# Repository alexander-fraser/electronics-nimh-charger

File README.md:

# electronics-nimh-charger
A simple NIMH AA or AAA battery charger based on bigclivedotcom's design.

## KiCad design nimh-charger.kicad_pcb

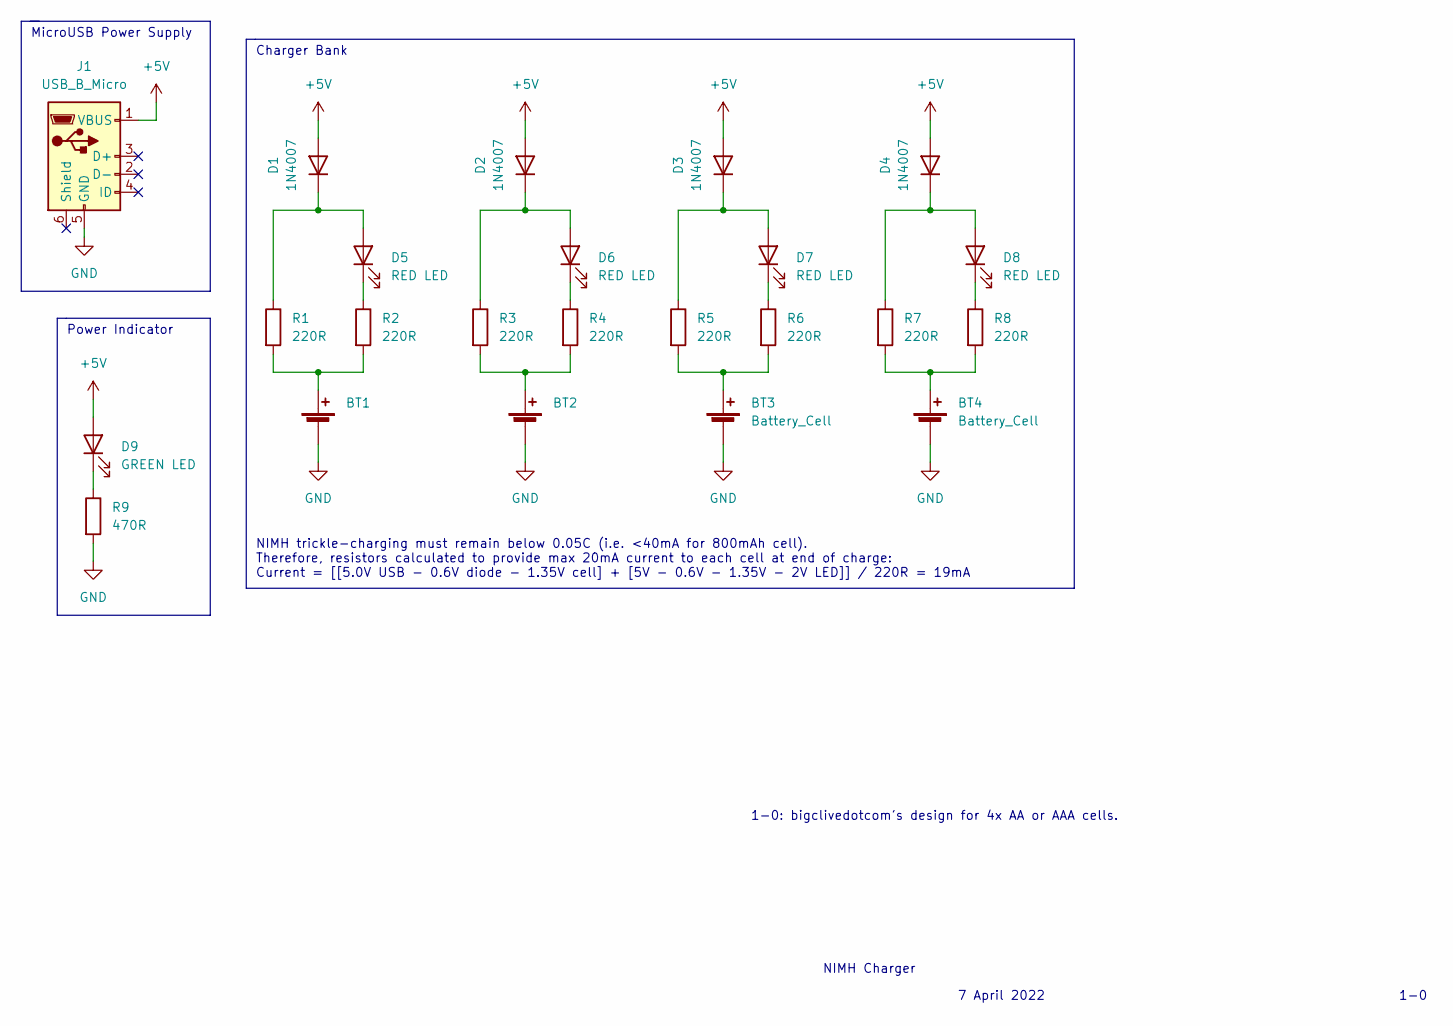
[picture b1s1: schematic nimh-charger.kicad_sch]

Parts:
BT1, BT2: (no value)
BT3, BT4: Battery_Cell
D1, D2, D3, D4: 1N4007; D_SOD-123F
D5, D6, D7, D8: RED LED; LED_1206_3216Metric_Pad1.42x1.75mm_HandSolder
D9: GREEN LED; LED_1206_3216Metric_Pad1.42x1.75mm_HandSolder
J1: USB_B_Micro; USB_Micro-B_Amphenol_10118194_Horizontal
R1, R2, R3, R4, R5, R6, R7, R8: 220R; R_1206_3216Metric_Pad1.30x1.75mm_HandSolder
R9: 470R; R_1206_3216Metric_Pad1.30x1.75mm_HandSolder

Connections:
+5V: D1.2 (A), D2.2 (A), D3.2 (A), D4.2 (A), D9.2 (A), J1.1 (VBUS)
GND: BT1.2 (-), BT2.2 (-), BT3.2 (-), BT4.2 (-), J1.5 (GND), R9.2
unnamed: BT1.1 (+), R1.2, R2.2
unnamed: BT2.1 (+), R3.2, R4.2
unnamed: BT3.1 (+), R5.2, R6.2
unnamed: BT4.1 (+), R7.2, R8.2
unnamed: D1.1 (K), D5.2 (A), R1.1
unnamed: D2.1 (K), D6.2 (A), R3.1
unnamed: D3.1 (K), D7.2 (A), R5.1
unnamed: D4.1 (K), D8.2 (A), R7.1
unnamed: D5.1 (K), R2.1
unnamed: D6.1 (K), R4.1
unnamed: D7.1 (K), R6.1
unnamed: D8.1 (K), R8.1
unnamed: D9.1 (K), R9.1

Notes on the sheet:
MicroUSB Power Supply
1-0
NIMH trickle-charging must remain below 0.05C (i.e. <40mA for 800mAh cell). Therefore, resistors calculated to provide max 20mA current to each cell at end of charge: Current = [[5.0V USB - 0.6V diode - 1.35V cell] + [5V - 0.6V - 1.35V - 2V LED]] / 220R = 19mA
Charger Bank
Power Indicator
7 April 2022
1-0: bigclivedotcom's design for 4x AA or AAA cells.
NIMH Charger

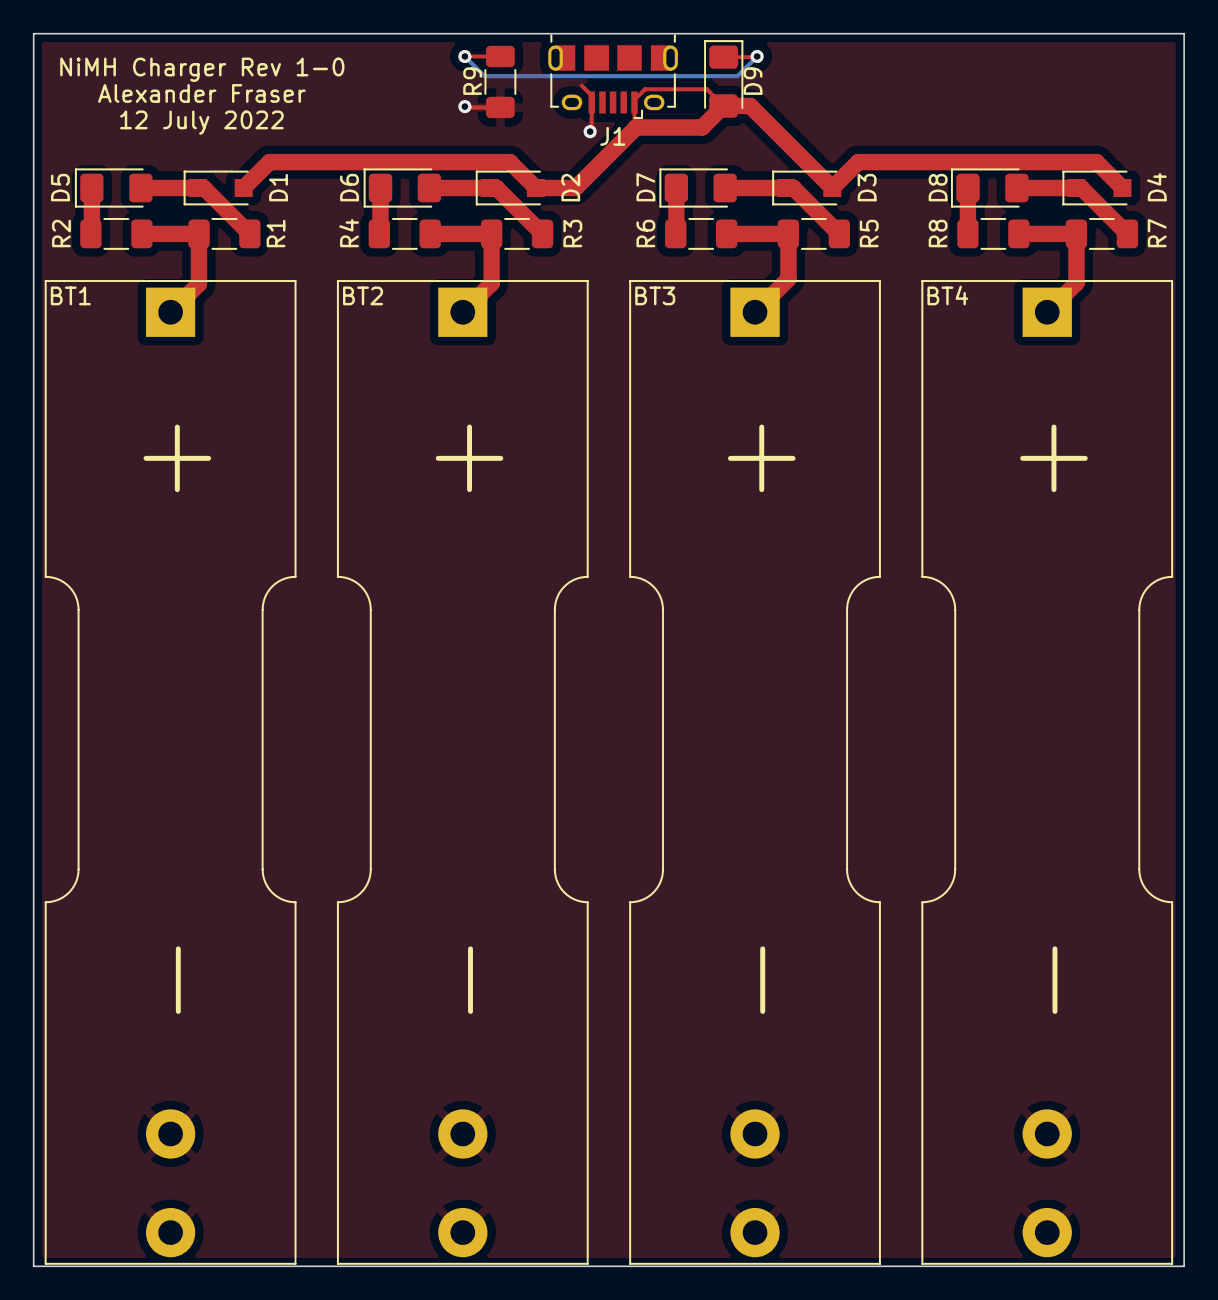
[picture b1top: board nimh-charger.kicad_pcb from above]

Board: 2 copper layers, 70.0 x 75.0 mm, 23 parts (0 on the bottom side), 15 nets.

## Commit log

2022-04-08 Add schematic with annotations.
2022-07-13 Assign PCB layouts.
2022-07-13 Create and assign cell holder layout.
2022-07-13 Create PCB layout.
2022-07-13 Generate plots.
2022-07-13 Add drill files to gerbers.
